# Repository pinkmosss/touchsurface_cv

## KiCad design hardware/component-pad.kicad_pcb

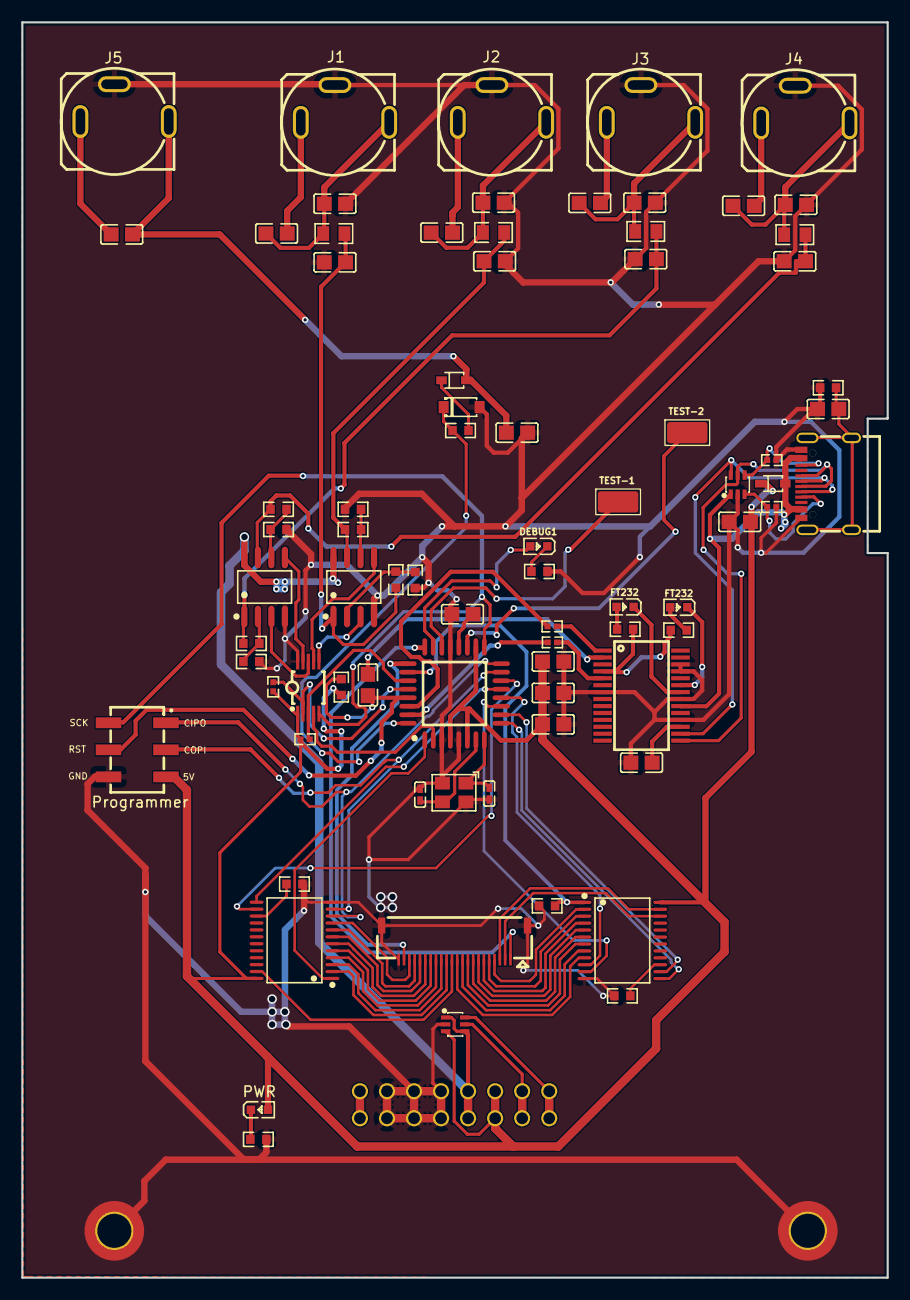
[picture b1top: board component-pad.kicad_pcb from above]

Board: 2 copper layers, 81.3 x 117.9 mm, 80 parts (1 on the bottom side), 93 nets.

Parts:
C1, C5, C8, C9, C11, C12, C14, C16, C18, C19, C20, C21, C22, C23, C24: 100nF; C0805
C2, C6, C7, C10, C13, C15, C17: 10uF; C0805
C3, C4: 15pf; C0402
CN1: FH55-22S-0.5SH; FPC-SMD_22P-P0.50_FH55-22S-0.5SH
CN2: PM254-2-03-S-8.5; HDR-SMD_6P-P2.54-V-F-R2-C3-LS7.0
D1, D2: SMF05CT1G; SOT-363_L2.0-W1.3-P0.65-LS2.1-BR
D3, D4: 1N5819WS; SOD-323_L1.8-W1.3-LS2.5-RD
J1, J2, J3, J4, J5: PJ-3411; AUDIO-TH_PJ-3411
LED1, LED2: Red; LED0603-RD
LED3, LED4: KT-0603R; LED0603-RD
P1: Eurorack Power; IDC-TH_16P-P2.54_C3406
R1: 1M; R0603
R2, R3: 5.1k; R0402
R4, R5, R30, R31: 330; R0603
R6, R9, R10, R11, R12, R13, R14, R15, R16, R17, R18, R24: 10k; R0603
R7, R8: 4.7k; R0402
R19, R20, R21, R22: 100; R0805
R27, R28: 1k; R0402
R29: 100k; R0603
TEST-1, TEST-2: TestPoint_Keystone_5019_Miniature
U1: MCP4728-E/UN; MSOP-10_L3.0-W3.0-P0.50-LS5.0-TL
U2: ATMEGA328-AU; TQFP-32_L7.0-W7.0-P0.80-LS9.0-BL
U3: FT232RNL-REEL; SSOP28_L10.2-W5.3-P0.65-LS7.8-BL
U4, U5: CD74HC4067SM96; SSOP-24_L8.1-W5.3-P0.65-LS7.8-BL
U6, U7: MCP6002T-I/SN; SOIC-8_L4.9-W3.9-P1.27-LS6.0-BL
USB1: TYPE-C16PIN; USB-C-SMD_TYPE-C16PIN
X1: X322516MLB4SI; OSC-SMD_4P-L3.2-W2.5-BL
ZD1: BZT52C5V1; SOD-123_L2.8-W1.8-LS3.7-RD

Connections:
AVR_RST: C5.1, CN2.5, R6.1, U2.29 (~PC6(RESET/PCINT14))
CAP1: CN1.1, U2.24 (PC1(ADC1/PCINT9))
CAP2: CN1.21, U2.25 (PC2(ADC2/PCINT10))
CC_1: D1.3, R3.1, USB1.A5 (CC1)
CC_2: D1.4, R2.1, USB1.B5 (CC2)
CIPO: CN2.1, U2.16 ((PCINT4/MISO)PB4), U4.10 (S0)
COPI: CN2.2, U2.15 ((PCINT3/OC2A/MOSI)PB3), U4.11 (S1)
DAC_LDAC: U1.4 (~LDAC), U2.2 ((PCINT20/XCK/T0)PD4)
DAC_OUT1: U1.6 (VOUTA), U6.3 (+INA)
DAC_OUT2: U1.7 (VOUTB), U6.5 (+INB)
DAC_OUT3: U1.8 (VOUTC), U7.3 (+INA)
DAC_OUT4: U1.9 (VOUTD), U7.5 (+INB)
DAC_RDY: CN2.6, U1.5 (RDY/~BSY), U2.17 (PB5(SCK/PCINT5))
DAC_SCL: R7.1, U1.2 (SCL), U2.28 (PC5(ADC5/SCL/PCINT13))
DAC_SDA: R8.1, U1.3 (SDA), U2.27 (PC4(ADC4/SDA/PCINT12))
DBUG1: LED4.2 (A), U2.23 (PC0(ADC0/PCINT8))
ER_CV: D2.5, P1.13, P1.14
ER_GATE: D2.6, P1.15, P1.16
ER_NEG_12V: P1.1, P1.2
ER_POS_5V: C2.1, C6.2, C7.2, C8.2, CN2.3, D2.3, D3.1 (K), LED3.2 (A), P1.11, P1.12, R6.2, R7.2, R8.2, U1.1 (VDD), U2.4 (VCC), U2.6 (VCC), U2.18 (AVCC), U4.24 (VCC), U5.24 (VCC)
ER_POS_12V: D2.1, D2.4, P1.9, P1.10, U6.8 (VDD), U7.8 (VDD)
FT_DTR: C5.2, U3.2 (~DTR)
FT_RXD: R28.1, U2.31 (PD1(TXD/PCINT17))
FT_TXD: R27.1, U2.30 (PD0(RXD/PCINT16))
FT_VCCIO: R30.2, R31.2, U3.4 (VCCIO)
GND: C1.2, C2.2, C3.1, C4.1, C6.1, C7.1, C8.1, C9.2, C10.2, C11.2, C12.2, C13.2, C14.2, C15.2, C16.2, C17.2, C18.2, C19.1, CN1.0, CN1.22, CN2.4, D1.2, D2.2, J1.5, J2.5, J3.5, J4.5, J5.5, P1.3, P1.4, P1.5, P1.6, P1.7, P1.8, R1.1, R2.2, R3.2, R4.1, R5.1, R9.2, R10.2, R12.1, R14.1, R16.1, R18.1, R29.2, U1.10 (VSS), U2.3 (GND), U2.5 (GND), U2.21 (GND), U3.7 (GND), U3.18 (GND), U3.21 (GND), U3.25 (AGND), U3.26 (TEST), U4.12 (GND), U5.12 (GND), U6.4 (-VSS), U7.4 (-VSS), USB1.A1B12 (GND), USB1.B1A12 (GND), X1.2 (GND), X1.4 (GND), ZD1.2 (A)
unnamed: C1.1, R1.2, USB1.1 (SHELL), USB1.2 (SHELL), USB1.3 (SHELL), USB1.4 (SHELL)
unnamed: C11.1, C20.1, J2.3, R19.1
unnamed: C12.1, C21.1, J1.3, R20.1
unnamed: C14.1, C23.1, J3.3, R21.1
unnamed: C16.1, C22.1, J4.3, R22.1
unnamed: C20.2, J2.2
unnamed: C21.2, J1.2
unnamed: C22.2, J4.2
unnamed: C23.2, J3.2
unnamed: C24.2, J5.2
unnamed: C18.1, C24.1, D4.2 (A), J5.3
unnamed: D4.1 (K), R24.2
unnamed: LED1.2 (A), R31.1
unnamed: LED1.1 (K), U3.22 (CBUS1)
unnamed: LED2.2 (A), R30.1
unnamed: LED2.1 (K), U3.23 (CBUS0)
unnamed: LED3.1 (K), R4.2
unnamed: LED4.1 (K), R5.2
unnamed: C3.2, U2.7 ((PCINT6/XTAL1/TOSC1)PB6), X1.3 (OSC2)
unnamed: C4.2, U2.8 ((PCINT7/XTAL2/TOSC2)PB7), X1.1 (OSC1)
unnamed: C9.1, U2.20 (AREF)
unnamed: C19.2, U3.17 (3V3OUT)
unnamed: R28.2, U3.5 (RXD)
unnamed: R27.2, U3.1 (TXD)
unnamed: R9.1, U4.15 (~E)
unnamed: R10.1, U5.15 (~E)
unnamed: R11.2, R12.2, U6.2 (-INA)
unnamed: R13.1, R14.2, U6.6 (-INB)
unnamed: R15.2, R16.2, U7.2 (-INA)
unnamed: R17.1, R18.2, U7.6 (-INB)
OUT1: C10.1, R11.1, R20.2, U6.1 (OUTA)
OUT2: C13.1, R13.2, R19.2, U6.7 (OUTB)
OUT3: C15.1, R15.1, R21.2, U7.1 (OUTA)
OUT4: C17.1, R17.2, R22.2, U7.7 (OUTB)
RX_ADC: R29.1, U2.26 (PC3(ADC3/PCINT11)), U5.1 (COMMONINOUT/OUTPUT)
RX_SEL0: U2.12 ((PCINT0/CLKO/ICP1)PB0), U5.10 (S0)
RX_SEL1: U2.11 ((PCINT23/AIN1)PD7), U5.11 (S1)
RX_SEL2: U2.10 ((PCINT22/OC0A/AIN0)PD6), U5.14 (S2)
RX_SEL3: U2.9 ((PCINT21/OC0B/T1)PD5), U5.13 (S3)
RX_SIGNAL_0: CN1.11, U5.9 (I0)
RX_SIGNAL_1: CN1.10, U5.8 (I1)
RX_SIGNAL_2: CN1.9, U5.7 (I2)
RX_SIGNAL_3: CN1.8, U5.6 (I3)
RX_SIGNAL_4: CN1.7, U5.5 (I4)
RX_SIGNAL_5: CN1.6, U5.4 (I5)
RX_SIGNAL_6: CN1.5, U5.3 (I6)
RX_SIGNAL_7: CN1.4, U5.2 (I7)
RX_SIGNAL_8: CN1.3, U5.23 (I8)
RX_SIGNAL_9: CN1.2, U5.22 (I9)
TEST1: TEST-1.1, U2.22 (ADC7)
TEST2: TEST-2.1, U2.19 (ADC6)
TRIG: R24.1, U2.32 (PD2(INT0/PCINT18)), ZD1.1 (K)
TX_PWM: U2.1 ((PCINT19/OC2B/INT1)PD3), U4.1 (COMMONINOUT/OUTPUT)
TX_SEL2: U2.14 ((PCINT2/SS/OC1B)PB2), U4.14 (S2)
TX_SEL3: U2.13 ((PCINT1/OC1A)PB1), U4.13 (S3)
TX_SIGNAL_0: CN1.20, U4.9 (I0)
TX_SIGNAL_1: CN1.19, U4.8 (I1)
TX_SIGNAL_2: CN1.18, U4.7 (I2)
TX_SIGNAL_3: CN1.17, U4.6 (I3)
TX_SIGNAL_4: CN1.16, U4.5 (I4)
TX_SIGNAL_5: CN1.15, U4.4 (I5)
TX_SIGNAL_6: CN1.14, U4.3 (I6)
TX_SIGNAL_7: CN1.13, U4.2 (I7)
TX_SIGNAL_8: CN1.12, U4.23 (I8)
USB_DN: D1.6, U3.16 (USBDM), USB1.A7 (DN1), USB1.B7 (DN2)
USB_DP: D1.5, U3.15 (USBDP), USB1.A6 (DP1), USB1.B6 (DP2)
VBUS: D1.1, D3.2 (A), U3.20 (VCC), USB1.A4B9 (VBUS), USB1.B4A9 (VBUS)

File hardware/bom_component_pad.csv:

Designator,Footprint,Quantity,Value,LCSC Part #
"C1, C11, C12, C14, C16, C18, C19, C20, C21, C22, C23, C24, C5, C8, C9",C0805,15,100nF,C28233
"C10, C13, C15, C17, C2, C6, C7",C0805,7,10uF,C440198
"C3, C4",C0402,2,15pf,C1548
CN1,FPC-SMD_22P-P0.50_FH55-22S-0.5SH,1,FH55-22S-0.5SH,C5182313
CN2,HDR-SMD_6P-P2.54-V-F-R2-C3-LS7.0,1,PM254-2-03-S-8.5,C3975148
"D1, D2",SOT-363_L2.0-W1.3-P0.65-LS2.1-BR,2,SMF05CT1G,C15879
"D3, D4",SOD-323_L1.8-W1.3-LS2.5-RD,2,1N5819WS,C191023
"J1, J2, J3, J4, J5",AUDIO-TH_PJ-3411,5,PJ-3411,C381132
"LED1, LED2",LED0603-RD,2,Red,C2286
"LED3, LED4",LED0603-RD,2,KT-0603R,C2286
P1,IDC-TH_16P-P2.54_C3406,1,Eurorack Power,C3406
R1,R0603,1,1M,C22935
"R10, R11, R12, R13, R14, R15, R16, R17, R18, R24, R6, R9",R0603,12,10k,C25804
"R19, R20, R21, R22",R0805,4,100,C17408
"R2, R3",R0402,2,5.1k,C25905
"R27, R28",R0402,2,1k,C11702
R29,R0603,1,100k,C73806
"R30, R31, R4, R5",R0603,4,330,C23138
"R7, R8",R0402,2,4.7k,C25900
"TEST-1, TEST-2",TestPoint_Keystone_5019_Miniature,2,TestPoint_Keystone_5019_Miniature,
U1,MSOP-10_L3.0-W3.0-P0.50-LS5.0-TL,1,MCP4728-E/UN,C108207
U2,TQFP-32_L7.0-W7.0-P0.80-LS9.0-BL,1,ATMEGA328-AU,C618731
U3,SSOP28_L10.2-W5.3-P0.65-LS7.8-BL,1,FT232RNL-REEL,C5246810
"U4, U5",SSOP-24_L8.1-W5.3-P0.65-LS7.8-BL,2,CD74HC4067SM96,C98457
"U6, U7",SOIC-8_L4.9-W3.9-P1.27-LS6.0-BL,2,MCP6002T-I/SN,C7377
USB1,USB-C-SMD_TYPE-C16PIN,1,TYPE-C16PIN,C393939
X1,OSC-SMD_4P-L3.2-W2.5-BL,1,X322516MLB4SI,C13738
ZD1,SOD-123_L2.8-W1.8-LS3.7-RD,1,BZT52C5V1,C2117
